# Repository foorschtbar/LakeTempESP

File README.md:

# LakeTempESP

WIP...

## Hardware 2021

## Hardware 2011-2021

One of my first electronic projects 2011 based on a breadboard. It has lasted almost 10 years of continuous operation.

- Arduino Uno
- Ethernet Shield (WIZnet W1500)
- BT42008 LCD (HD44780 4x20)
- WiFi AP in Client Mode
- 5V Power Suppy for the Arduino
- 12V Power Suppy for the AccessPoint

## ToDo
- [ ] Fix random HW/SW watchdog reboots while uploading data
- [ ] Use Light Sensor for nice things
- [x] Trigger data upload from WebUI
- [x] Show last und next upload on Dashboard
- [x] Add MAC Address to JSON Msg
- [x] Flash/Blink LED on Upload
- [x] Flash/Blink LED on Button press
- [x] Fade LED in Idle State

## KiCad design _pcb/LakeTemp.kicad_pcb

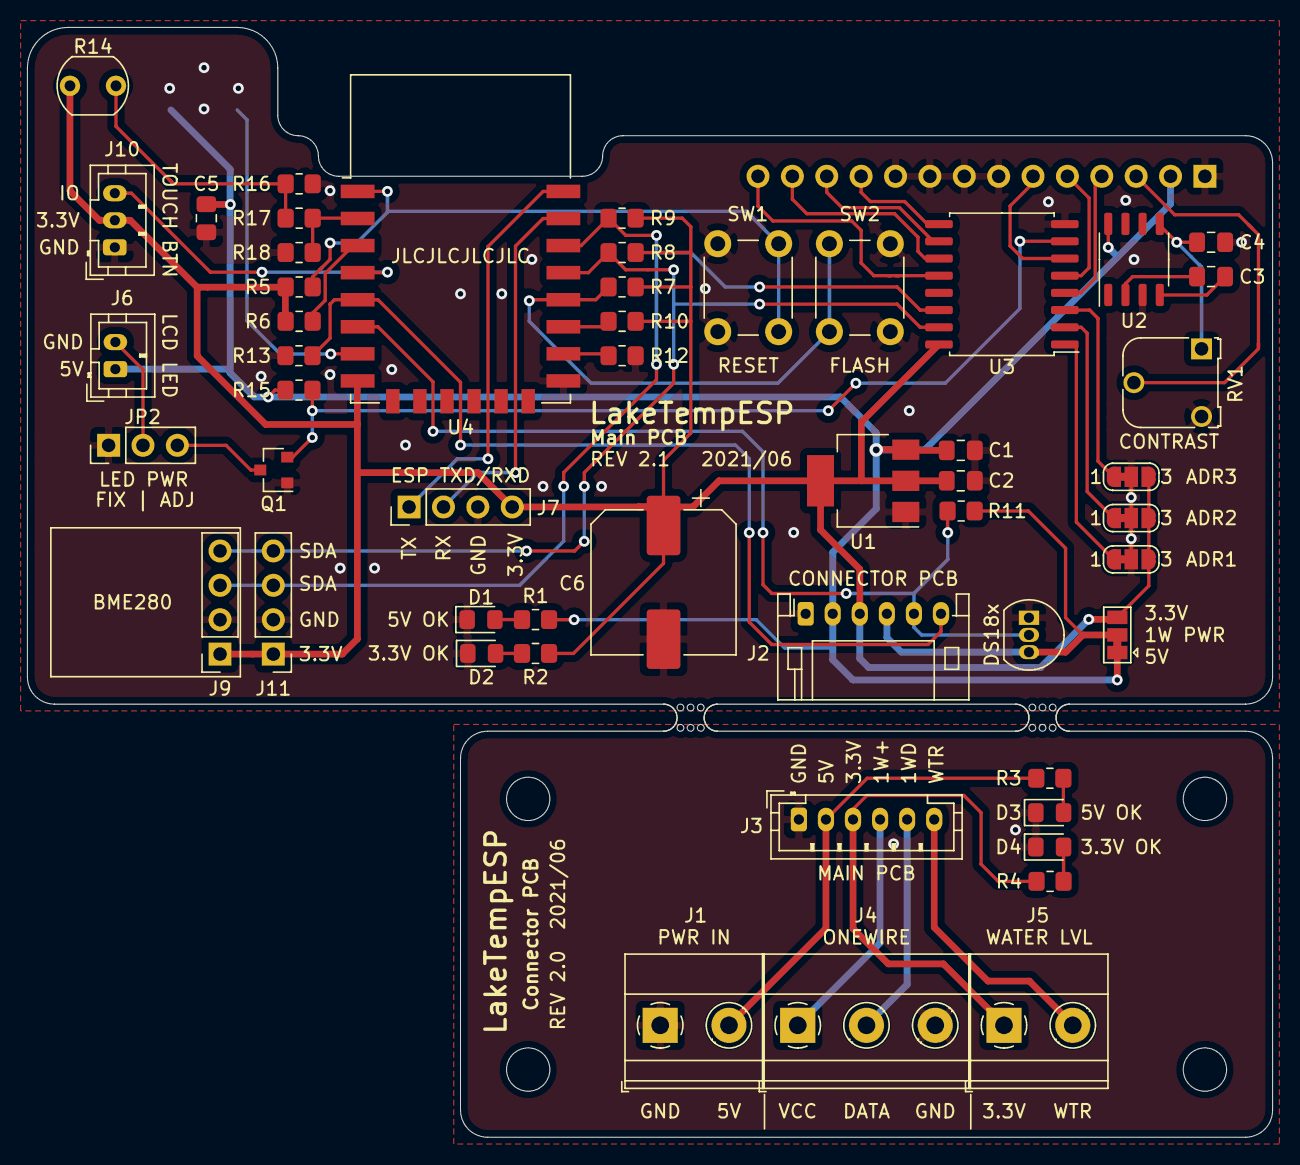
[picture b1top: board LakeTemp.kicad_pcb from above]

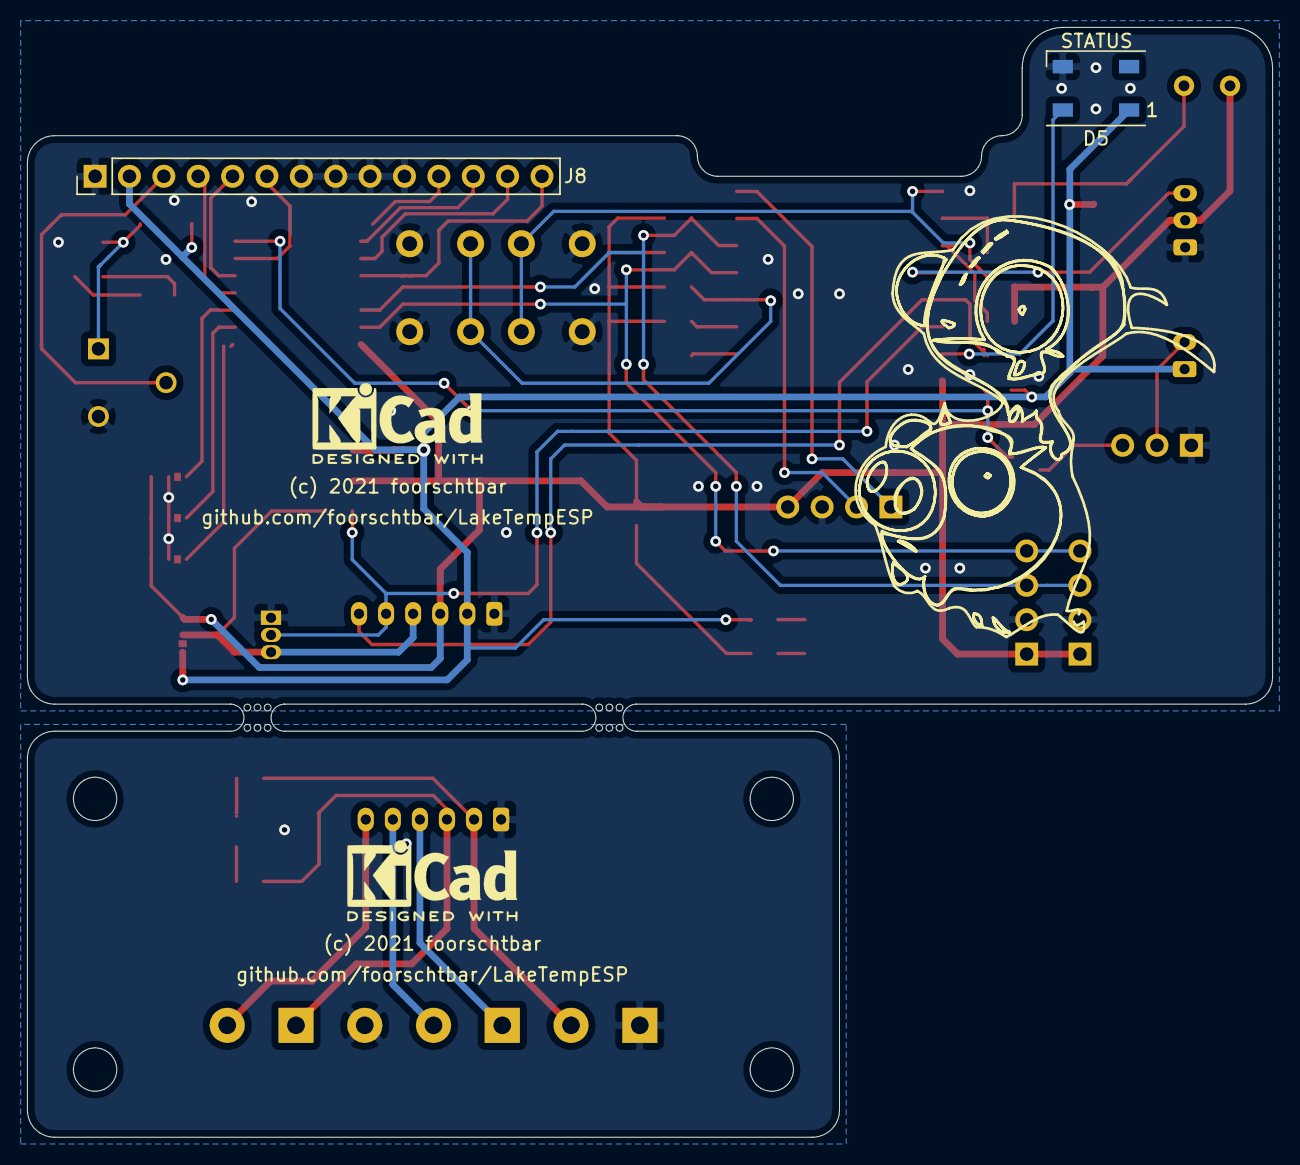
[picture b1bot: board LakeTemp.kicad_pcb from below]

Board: 2 copper layers, 92.0 x 82.0 mm, 56 parts (2 on the bottom side), 46 nets.

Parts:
ADR-A1, ADR-A2, ADR-A3: SolderJumper_2_Open; SolderJumper-3_P1.3mm_Bridged12_RoundedPad1.0x1.5mm_NumberL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
C1, C2, C3, C4: 10uF; C_0805_2012Metric_Pad1.18x1.45mm_HandSolder
C5: 100nF; C_0805_2012Metric_Pad1.18x1.45mm_HandSolder
C6: 1000uF; CP_Elec_10x10.5
D1, D3: PWR 5V; LED_0805_2012Metric_Pad1.15x1.40mm_HandSolder
D2, D4: PWR 3.3V; LED_0805_2012Metric_Pad1.15x1.40mm_HandSolder
D5: WS2812B; LED_WS2812B_PLCC4_5.0x5.0mm_P3.2mm
J1, J5: Conn_01x02_Female; TerminalBlock_Phoenix_MKDS-1,5-2-5.08_1x02_P5.08mm_Horizont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
J2: Conn_01x06_Male; JST_PH_S6B-PH-K_1x06_P2.00mm_Horizontal
J3: Conn_01x06_Male; JST_PH_B6B-PH-K_1x06_P2.00mm_Vertical
J4: Conn_01x03_Female; TerminalBlock_Phoenix_MKDS-1,5-3-5.08_1x03_P5.08mm_Horizont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
J6: Conn_01x02_Female; JST_PH_B2B-PH-K_1x02_P2.00mm_Vertical
J7: Conn_01x04_Male; PinHeader_1x04_P2.54mm_Vertical
J8: Conn_01x14_Female; PinHeader_1x14_P2.54mm_Vertical
J9: Conn_01x04_Female; PinSocket_1x04_P2.54mm_Vertical
J10: Conn_01x03_Male; JST_PH_B3B-PH-K_1x03_P2.00mm_Vertical
J11: Conn_01x04_Female; PinHeader_1x04_P2.54mm_Vertical
JP1: SolderJumper_3_Open; SolderJumper-3_P1.3mm_Bridged12_Pad1.0x1.5mm
JP2: SolderJumper_3_Open; PinHeader_1x03_P2.54mm_Vertical
Q1: S8050; SOT-23
R1, R3: 150; R_0805_2012Metric_Pad1.20x1.40mm_HandSolder
R2, R4: 68; R_0805_2012Metric_Pad1.20x1.40mm_HandSolder
R5, R6, R7, R10, R12, R16: 10K; R_0805_2012Metric_Pad1.20x1.40mm_HandSolder
R8, R9, R11, R13, R15: 4,7K; R_0805_2012Metric_Pad1.20x1.40mm_HandSolder
R14: GL5528; R_LDR_5.1x4.3mm_P3.4mm_Vertical
R17: 220K; R_0805_2012Metric_Pad1.20x1.40mm_HandSolder
R18: 100K; R_0805_2012Metric_Pad1.20x1.40mm_HandSolder
RV1: 10K; Potentiometer_Runtron_RM-065_Vertical
SW1: RESET; SW_PUSH_6mm_H5mm
SW2: FLASH; SW_PUSH_6mm_H5mm
U1: NCP1117-3.3_SOT223; SOT-223-3_TabPin2
U2: ICL7660; SOP-8_3.9x4.9mm_P1.27mm
U3: PCF8574; SOIC-16W_7.5x10.3mm_P1.27mm
U4: ESP-12E
U5: DS18B20; TO-92_Inline
mouse-bite-2mm-slot, mouse-bite-2mm-slot#2: VAL**; mouse-bite-2mm-slot

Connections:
+3V3: ADR-A1.3, ADR-A2.3, ADR-A3.3, C2.1, C6.1, J2.3, J7.4, J9.1, J10.2, J11.1, JP1.3, R2.1, R5.2, R6.2, R7.2, R8.1, R9.1, R10.2, R14.1, U1.2, U3.16, U4.8
+5V: C1.1, C5.1, D5.1, J2.2, J6.1, J8.2, JP1.1, R1.1, R15.1, U1.3, U2.8
ESP_RX: J7.2, U4.21
ESP_TX: J7.1, U4.22
GND: ADR-A1.2, ADR-A2.2, ADR-A3.2, C1.2, C2.2, C4.2, C5.2, C6.2, D1.1, D2.1, D5.3, J2.1, J7.3, J8.1, J8.7, J8.8, J8.9, J8.10, J9.2, J10.1, J11.2, JP2.1, Q1.1, R12.1, R13.2, R16.2, R18.1, RV1.3, SW1.1, SW2.1, U1.1, U2.3, U3.8, U4.15, U5.1
GND1: D3.1, D4.1, J1.1, J3.1, J4.3
LCD_CONTRAST: J8.3, RV1.2
LCD_DB4: J8.11, U3.9
LCD_DB5: J8.12, U3.10
LCD_DB6: J8.13, U3.11
LCD_DB7: J8.14, U3.12
LCD_E: J8.6, U3.6
LCD_LED: Q1.2, R15.2, U3.7
LCD_RS: J8.4, U3.4
LCD_RW: J8.5, U3.5
LDR: R14.2, R16.1, R17.2
unnamed: C3.1, U2.2
unnamed: C3.2, U2.4
unnamed: C4.1, RV1.1, U2.5
unnamed: D1.2, R1.2
unnamed: D2.2, R2.2
unnamed: D3.2, R3.2
unnamed: D4.2, R4.2
unnamed: J1.2, J3.2, R3.1
unnamed: J3.3, J5.1, R4.1
unnamed: J3.4, J4.1
unnamed: J3.5, J4.2
unnamed: J3.6, J5.2
unnamed: J6.2, JP2.2
unnamed: JP2.3, Q1.3
unnamed: R5.1, SW1.2, U4.1
unnamed: R6.1, U4.3
unnamed: R7.1, SW2.2, U4.18
unnamed: R10.1, U4.17
unnamed: R12.2, U4.16
unnamed: R17.1, R18.2, U4.2
ONEWIRE_BUS: J2.5, R11.2, U4.6, U5.2
ONEWIRE_PWR: J2.4, JP1.2, R11.1, U5.3
PCF_A0: ADR-A1.1, U3.1
PCF_A1: ADR-A2.1, U3.2
PCF_A2: ADR-A3.1, U3.3
SCL: J9.3, J11.3, R9.2, U3.14, U4.20
SDA: J9.4, J11.4, R8.2, U3.15, U4.19
TOUCH_IO: J10.3, U4.4
WATER_LEVEL: J2.6, R13.1, U4.5
WS2812B: D5.4, U4.7

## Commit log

2021-05-15 Inital commit
2021-05-15 Added PCB draft
2021-05-15 Added docu
2021-05-16 Moved Screens library to libs folder
2021-05-16 Removed travis CI file
2021-05-22 Added BME280 Support
2021-05-22 Update PCB
2021-05-22 Finished PCB v1.0
2021-05-22 Added Gerber files
2021-06-05 Added Gerber files for Rev 1.0 PCB
2021-06-05 Added Datasheet for NCP1117
2021-06-05 Updated PCB to REV 2.0
2021-06-05 Added Gerber-ZIP
2021-06-05 Added Labels to Aux I2C Connector
2021-06-05 Added Gerber Files for Main PCB Only (REV 2.0)
2021-06-26 Added ESP-12E Chip
2021-06-26 Added LED, Webserver, OTA, Screens and many more...
2021-06-28 Added HLK-PM01 datasheet
2021-06-28 Added modified NTPClient
2021-06-28 Replace config file with GUI settings page
2021-06-30 Extened Dashboard and upload msg
    - Trigger data upload from WebUI
    - Show last und next upload on Dashboard
    - Add MAC Address to JSON Msg
    - Flash/Blink LED on Upload
2021-07-02 Added some LED things
    - Flash LED on button press
    - Fade LED on Idle State
    - Serial output depends on build flag
2021-07-02 Replaced ifdef DEBUG with function
2021-12-25 Added wifi auto reconnect

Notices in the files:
_pcb/LakeTemp.kicad_pcb:
(c) 2021 foorschtbar
